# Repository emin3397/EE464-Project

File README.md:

# EE464-Project
Emin Ün-Emre Karabakla-Görkem Gülletutan

Rapor: 
https://docs.google.com/document/d/1F6ZsHuH_-bDFWWwnSLHJ_5yXT3tPWivFNy6Llo1I6zs/edit#heading=h.hhpnnwzfyg3q

Sunum:
https://docs.google.com/presentation/d/1tMdv5Q-z6gMAUCtrlJFETEWXZ9VnNtSR/edit#slide=id.p1

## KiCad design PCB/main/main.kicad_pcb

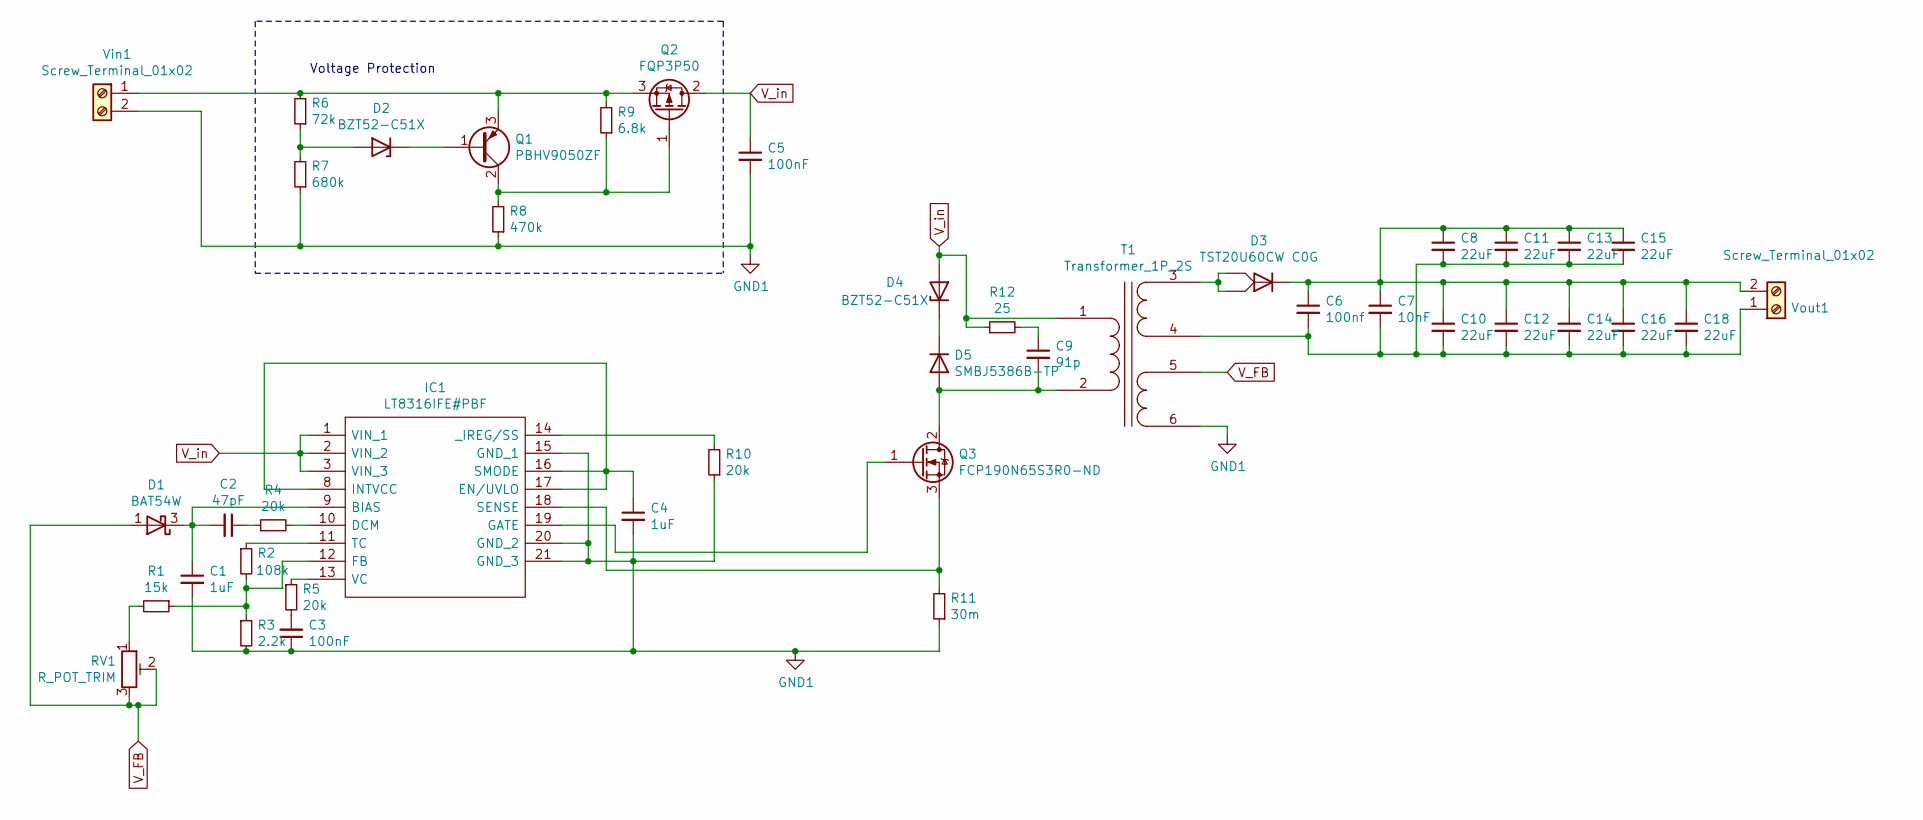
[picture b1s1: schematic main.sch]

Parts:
C1, C4: 1uF; C_0805_2012Metric
C2: 47pF; C_0805_2012Metric
C3, C5: 100nF; C_0805_2012Metric
C6: 100nf; C_0805_2012Metric
C7: 10nF; C_0805_2012Metric
C8, C10, C11, C12, C13, C14, C15, C16, C18: 22uF; C_1210_3225Metric
C9: 91p; C_0805_2012Metric
D1: BAT54W; SOT-323_SC-70
D2: BZT52-C51X; D_SOD-123
D3: TST20U60CW C0G; TO-220-3_Vertical
D4: BZT52-C51X; D_SMB
D5: SMBJ5386B-TP; D_SMA
IC1: LT8316IFE#PBF; LT8316IFEPBF; Manufacturer_Part_Number LT8316IFE#PBF; Mouser Part Number 584-LT8316IFE#PBF
Q1: PBHV9050ZF; SOT-223-3_TabPin2
Q2: FQP3P50; TO-220-3_Vertical
Q3: FCP190N65S3R0-ND; TO-220-3_Vertical
R1: 15k; R_0805_2012Metric
R2: 108k; R_0805_2012Metric
R3: 2.2k; R_0805_2012Metric
R4, R5, R10: 20k; R_0805_2012Metric
R6: 72k; R_0805_2012Metric
R7: 680k; R_0805_2012Metric
R8: 470k; R_0805_2012Metric
R9: 6.8k; R_0805_2012Metric
R11: 30m; R_1218_3246Metric_Pad1.22x4.75mm_HandSolder
R12: 25; R_0805_2012Metric
RV1: R_POT_TRIM; Potentiometer_Bourns_3314G_Vertical
T1: Transformer_1P_2S; EE464_Transformer
Vin1: Screw_Terminal_01x02; TerminalBlock_Altech_AK300-2_P5.00mm
Vout1: Screw_Terminal_01x02; TerminalBlock_Altech_AK300-2_P5.00mm

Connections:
GND1: C1.2, C3.1, C4.2, C5.2, IC1.15 (GND_1), IC1.20 (GND_2), IC1.21 (GND_3), R3.2, R7.1, R8.1, R10.1, R11.1, T1.6 (SD), Vin1.2
unnamed: C1.1, C2.2, D1.3 (K), IC1.9 (BIAS)
unnamed: C2.1, R4.1
unnamed: C3.2, R5.2
unnamed: C4.1, IC1.8 (INTVCC), IC1.16 (SMODE), IC1.17 (EN/UVLO)
unnamed: C9.1, R12.2
unnamed: C9.2, D5.1 (A), Q3.2 (D), T1.2 (AB)
unnamed: C6.1, C7.1, C8.1, C10.1, C11.1, C12.1, C13.1, C14.1, C15.1, C16.1, C18.1, D3.2 (K), Vout1.2
unnamed: C6.2, C7.2, C8.2, C10.2, C11.2, C12.2, C13.2, C14.2, C15.2, C16.2, C18.2, T1.4 (SB), Vout1.1
unnamed: D2.1 (K), Q1.1 (B)
unnamed: D2.2 (A), R6.1, R7.2
unnamed: D3.1 (A), D3.3 (A), T1.3 (SA)
unnamed: D4.1 (K), D5.2 (K)
unnamed: IC1.10 (DCM), R4.2
unnamed: IC1.11 (TC), R2.1
unnamed: IC1.12 (FB), R1.1, R2.2, R3.1
unnamed: IC1.13 (VC), R5.1
unnamed: IC1.14 (_IREG/SS), R10.2
unnamed: IC1.18 (SENSE), Q3.3 (S), R11.2
unnamed: IC1.19 (GATE), Q3.1 (G)
unnamed: Q1.2 (C), Q2.1 (G), R8.2, R9.1
unnamed: Q1.3 (E), Q2.3 (S), R6.2, R9.2, Vin1.1
unnamed: R1.2, RV1.1
V_FB: D1.1 (A), RV1.2, RV1.3, T1.5 (SC)
V_in: C5.1, D4.2 (A), IC1.1 (VIN_1), IC1.2 (VIN_2), IC1.3 (VIN_3), Q2.2 (D), R12.1, T1.1 (AA)

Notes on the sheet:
Voltage Protection

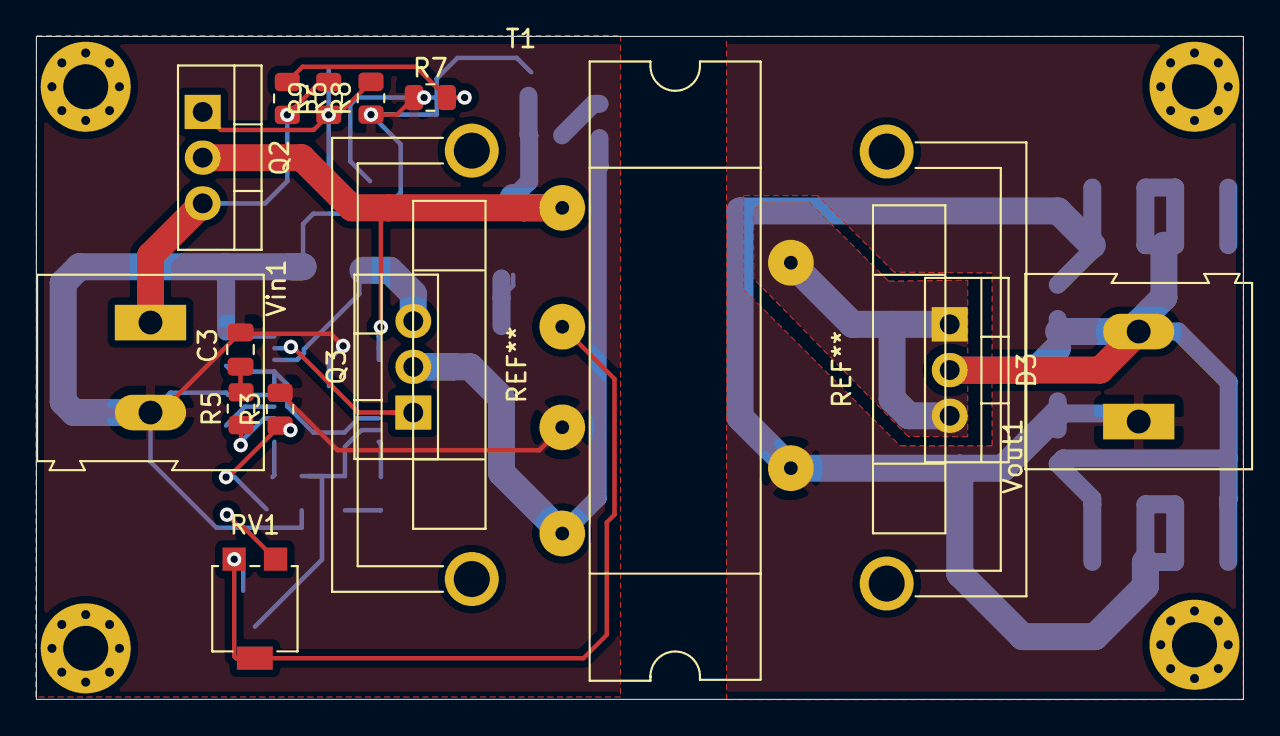
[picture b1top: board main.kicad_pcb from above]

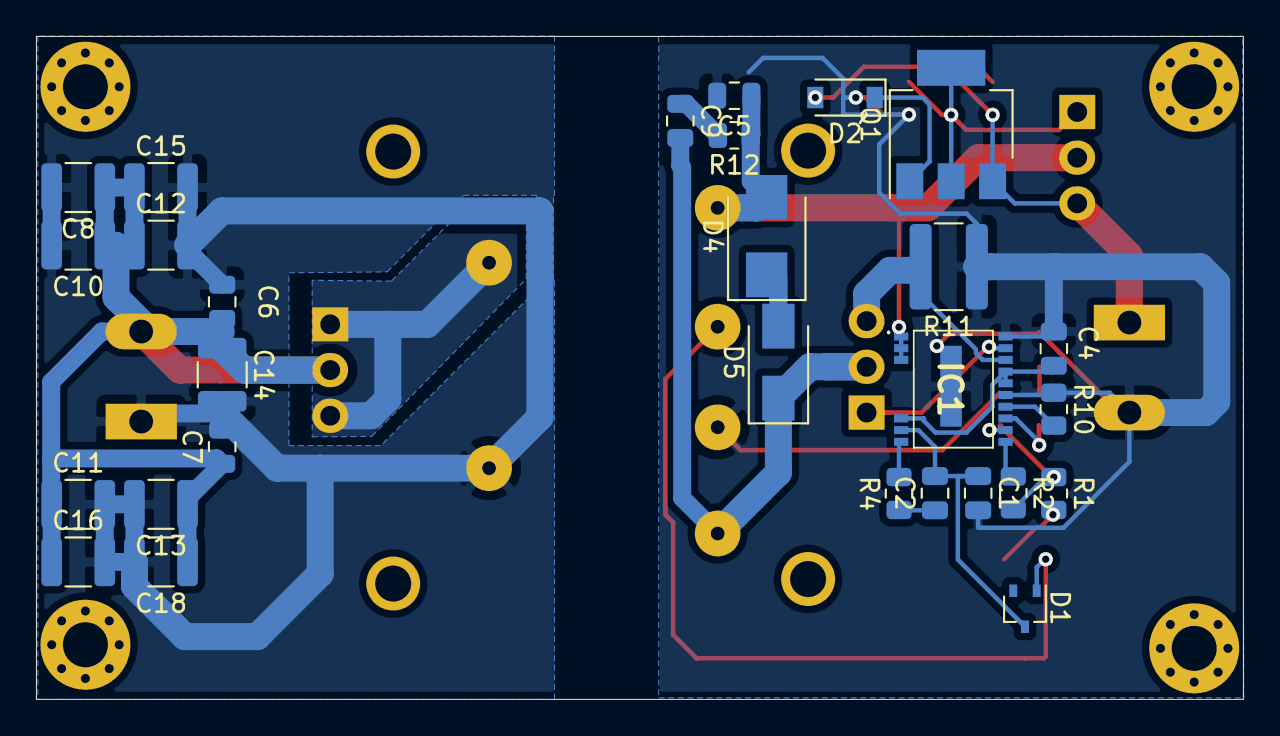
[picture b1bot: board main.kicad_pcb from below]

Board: 2 copper layers, 67.1 x 36.8 mm, 42 parts (28 on the bottom side), 25 nets.

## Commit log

2021-04-21 Report is added.
2021-04-25 Datasheet of our controller (LT 8316)
2021-04-25 Application note for flyback design (highlighted)
2021-04-25 Example of designing flyback converter with given specs (highlighted)
2021-04-25 Datasheet of our controller (LT 8316) (highlighted)
2021-04-27 selection_script
2021-04-27 m file updated
2021-04-28 Result section added
2021-04-28 tranformer calc updated
2021-04-28 protection circuit design
2021-04-29 Component Selection is added.
2021-04-29 Our design with selected components and controller
2021-04-30 The design is updated. (Sense resistance, output capacitance and transformer inductances are changed.)
2021-05-01 PCB drawing, components update
2021-05-02 pcb drawing update
2021-05-02 Component selection is updated.
2021-05-02 Complete Simulation Report is completed.
2021-05-06 PCB updated with new mosfet&diode
2021-05-07 Presentation template is added.
2021-05-07 Power losses and thermal analysis for Diode and MOSFET is completed.
2021-05-07 script and pcb updated
2021-07-01 Thermal simulation and box drawing
2021-07-02 The final report is almost finished.
2021-07-03 A grammer mistake is fixed.
